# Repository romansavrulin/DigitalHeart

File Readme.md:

# RDC1-0009, Цифровое сердце

Это цифровое, светодиодное сердце будет отличным подарком девушке ко Дню Влюбленных, 8 Марта, или на День рождения.
21 светодиод расположены по периметру печатной платы в виде сердца. Все они управляются микроконтроллером ATmega328. В демонстрационном скетче прописаны несколько эффектов оживляющих сердце. Скетч загружается с помощью любого контроллера Arduino. Но главная изюминка это вибромоторчик от смартфона расположенный на тыльной стороне. Он создает эффект бьющегося в такт световым эффектам сердца. Скетч легко изменить, если вы придумаете новые световые эффекты и частоту стука сердца. 
На тыльной стороне сердца есть зарядное устройство для Li-ion аккумуляторов, которое будет подзаряжать ваше сердце через порт Mini USB. Схема зарядного устройства собрана на микросхеме MCP73831T. Схема включения стандартная из описания на микросхему.
Все детали проекта открыты для свободного использования. Проект созданный в KiCAD можно скачать в приложении. Программу скачивайте в разделе «Скетч – код программы».

## Внешний вид устройства

## Технические параметры

Размер - 50 х 50 мм.
Источник питания – Li-Ion или Li-Pol аккумулятор 3,7В

## Programmer wiring

| Nano pins | NANO ISP PIN | Nano net | Target Net | Target Pin |
|-----|-----|-----|-----|----|
| D12 | 1 | MOSI | MISO | 1 |
| 5V  | 2 | 5V | 5V   | 2 |
| D13 | 3 | SCK | SCK  | 3 |
| D11 | 4 | MISO | MOSI | 4 |
| D10 | N/A, USE D10 | TARGET_RST | RST | 5  |
| GND | 6 | GND | GND  | 6 |

## Troubleshooting

If you get slow effects, it's wrong FUSE configuration. Try to run 

```
"C:\Program Files (x86)\Arduino\hardware\tools\avr/bin/avrdude" "-CC:\Program Files (x86)\Arduino\hardware\tools\avr/etc/avrdude.conf" -v -patmega168p -cstk500v1 -PCOM4 -b19200 -U lfuse:w:0xE2:m
```

from console

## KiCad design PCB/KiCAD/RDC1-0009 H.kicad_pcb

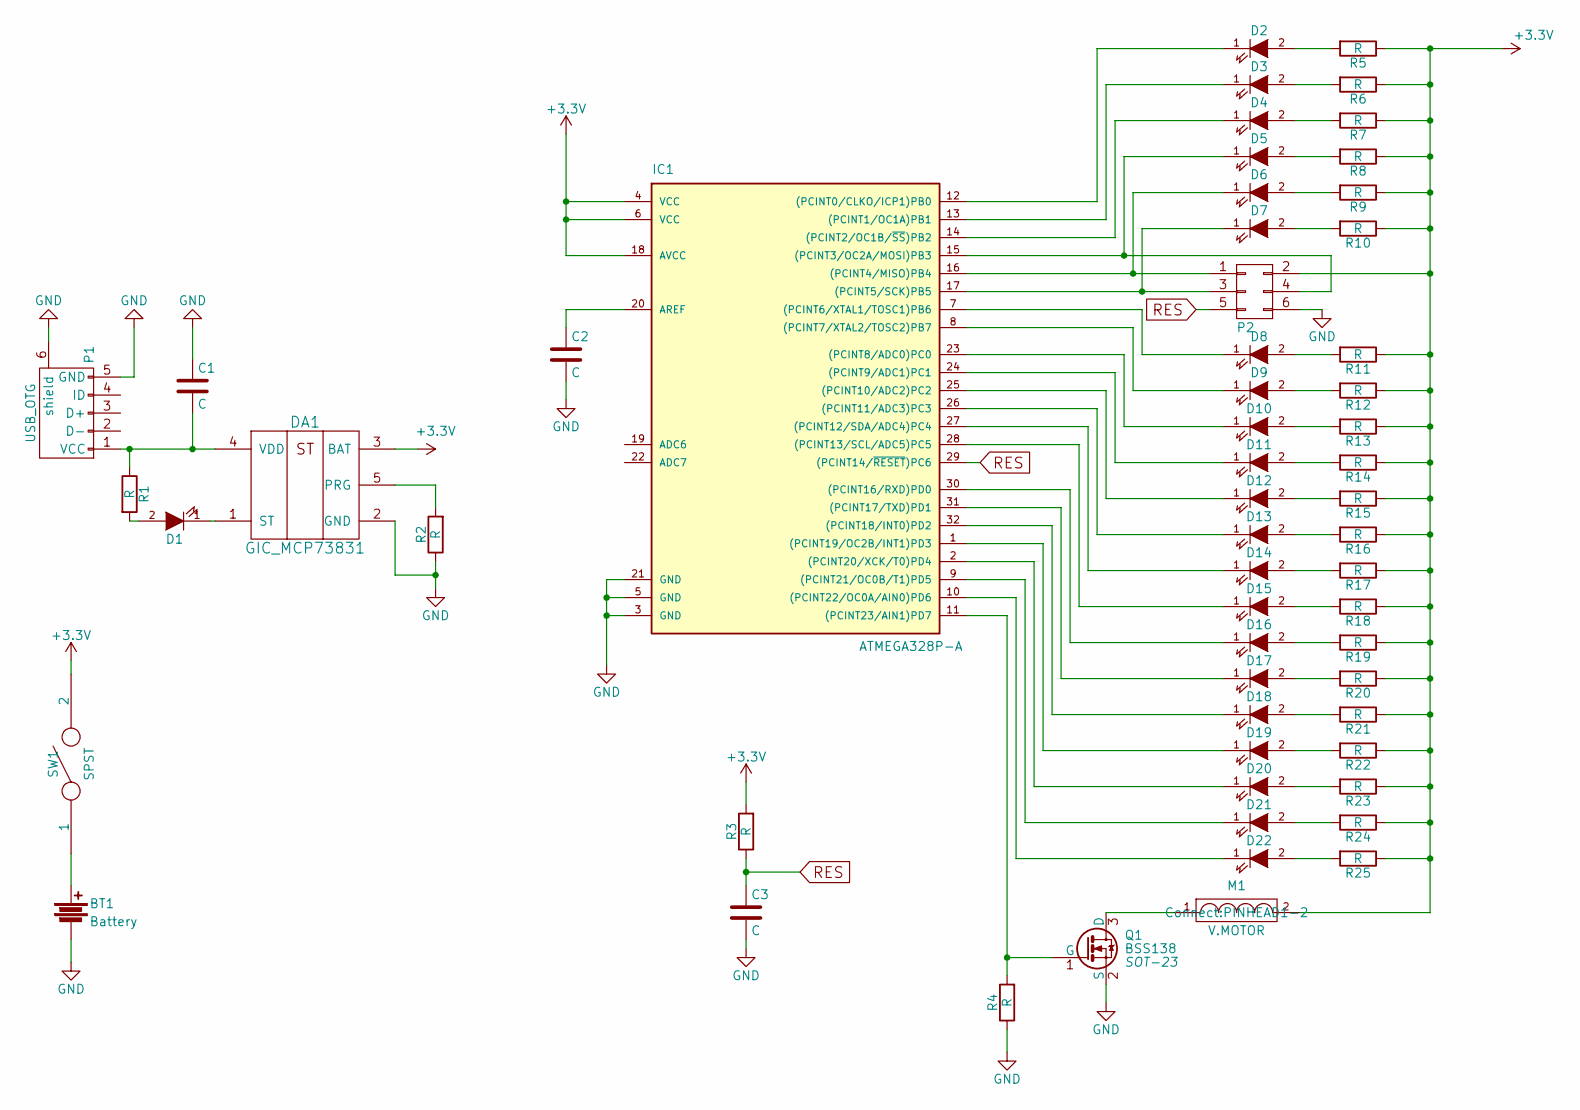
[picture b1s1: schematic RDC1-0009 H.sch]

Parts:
BT1: Battery; Pin_Header_Straight_1x02_mm
C1, C2, C3: C; C_0805_HandSoldering
D1, D2, D3, D4, D5, D6, D7, D8, D9, D10, D11, D12, D13, D14, D15, D16, D17, D18, D19, D20, D21, D22: LED; LED_0805
DA1: GIC_MCP73831; SOT-23-5_mm
IC1: ATMEGA328P-A; LQFP-32_7x7mm_Pitch0.8mm
M1: V.MOTOR; PINHEAD1-2
P1: USB_OTG; USB_Mini-B_mm
P2: CONN_02X03; Pin_Header_Straight_2x03_mm
Q1: BSS138; SOT-23
R1, R2, R3, R4, R5, R6, R7, R8, R9, R10, R11, R12, R13, R14, R15, R16, R17, R18, R19, R20, R21, R22, R23, R24, R25: R; R_0805_HandSoldering
SW1: SPST; SWITCH-mmp122-r

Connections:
+3V3: DA1.3 (BAT), IC1.4 (VCC), IC1.6 (VCC), IC1.18 (AVCC), M1.2, P2.2, R3.2, R5.1, R6.1, R7.1, R8.1, R9.1, R10.1, R11.1, R12.1, R13.1, R14.1, R15.1, R16.1, R17.1, R18.1, R19.1, R20.1, R21.1, R22.1, R23.1, R24.1, R25.1, SW1.2
GND: BT1.2, C1.1, C2.2, C3.2, DA1.2 (GND), IC1.3 (GND), IC1.5 (GND), IC1.21 (GND), P1.5 (GND), P1.6 (shield), P2.6, Q1.2 (S), R2.1, R4.1
unnamed: BT1.1, SW1.1
unnamed: C1.2, DA1.4 (VDD), P1.1 (VCC), R1.1
unnamed: C2.1, IC1.20 (AREF)
unnamed: D1.1 (K), DA1.1 (ST)
unnamed: D1.2 (A), R1.2
unnamed: D2.1 (K), IC1.12 ((PCINT0/CLKO/ICP1)PB0)
unnamed: D2.2 (A), R5.2
unnamed: D3.1 (K), IC1.13 ((PCINT1/OC1A)PB1)
unnamed: D3.2 (A), R6.2
unnamed: D4.1 (K), IC1.14 ((PCINT2/OC1B/~SS~)PB2)
unnamed: D4.2 (A), R7.2
unnamed: D5.1 (K), IC1.15 ((PCINT3/OC2A/MOSI)PB3), P2.4
unnamed: D5.2 (A), R8.2
unnamed: D6.1 (K), IC1.16 ((PCINT4/MISO)PB4), P2.1
unnamed: D6.2 (A), R9.2
unnamed: D7.1 (K), IC1.17 ((PCINT5/SCK)PB5), P2.3
unnamed: D7.2 (A), R10.2
unnamed: D8.1 (K), IC1.7 ((PCINT6/XTAL1/TOSC1)PB6)
unnamed: D8.2 (A), R11.2
unnamed: D9.1 (K), IC1.8 ((PCINT7/XTAL2/TOSC2)PB7)
unnamed: D9.2 (A), R12.2
unnamed: D10.1 (K), IC1.23 ((PCINT8/ADC0)PC0)
unnamed: D10.2 (A), R13.2
unnamed: D11.1 (K), IC1.24 ((PCINT9/ADC1)PC1)
unnamed: D11.2 (A), R14.2
unnamed: D12.1 (K), IC1.25 ((PCINT10/ADC2)PC2)
unnamed: D12.2 (A), R15.2
unnamed: D13.1 (K), IC1.26 ((PCINT11/ADC3)PC3)
unnamed: D13.2 (A), R16.2
unnamed: D14.1 (K), IC1.27 ((PCINT12/SDA/ADC4)PC4)
unnamed: D14.2 (A), R17.2
unnamed: D15.1 (K), IC1.28 ((PCINT13/SCL/ADC5)PC5)
unnamed: D15.2 (A), R18.2
unnamed: D16.1 (K), IC1.30 ((PCINT16/RXD)PD0)
unnamed: D16.2 (A), R19.2
unnamed: D17.1 (K), IC1.31 ((PCINT17/TXD)PD1)
unnamed: D17.2 (A), R20.2
unnamed: D18.1 (K), IC1.32 ((PCINT18/INT0)PD2)
unnamed: D18.2 (A), R21.2
unnamed: D19.1 (K), IC1.1 ((PCINT19/OC2B/INT1)PD3)
unnamed: D19.2 (A), R22.2
unnamed: D20.1 (K), IC1.2 ((PCINT20/XCK/T0)PD4)
unnamed: D20.2 (A), R23.2
unnamed: D21.1 (K), IC1.9 ((PCINT21/OC0B/T1)PD5)
unnamed: D21.2 (A), R24.2
unnamed: D22.1 (K), IC1.10 ((PCINT22/OC0A/AIN0)PD6)
unnamed: D22.2 (A), R25.2
unnamed: DA1.5 (PRG), R2.2
unnamed: IC1.11 ((PCINT23/AIN1)PD7), Q1.1 (G), R4.2
unnamed: M1.1, Q1.3 (D)
RES: C3.1, IC1.29 ((PCINT14/~RESET~)PC6), P2.5, R3.1

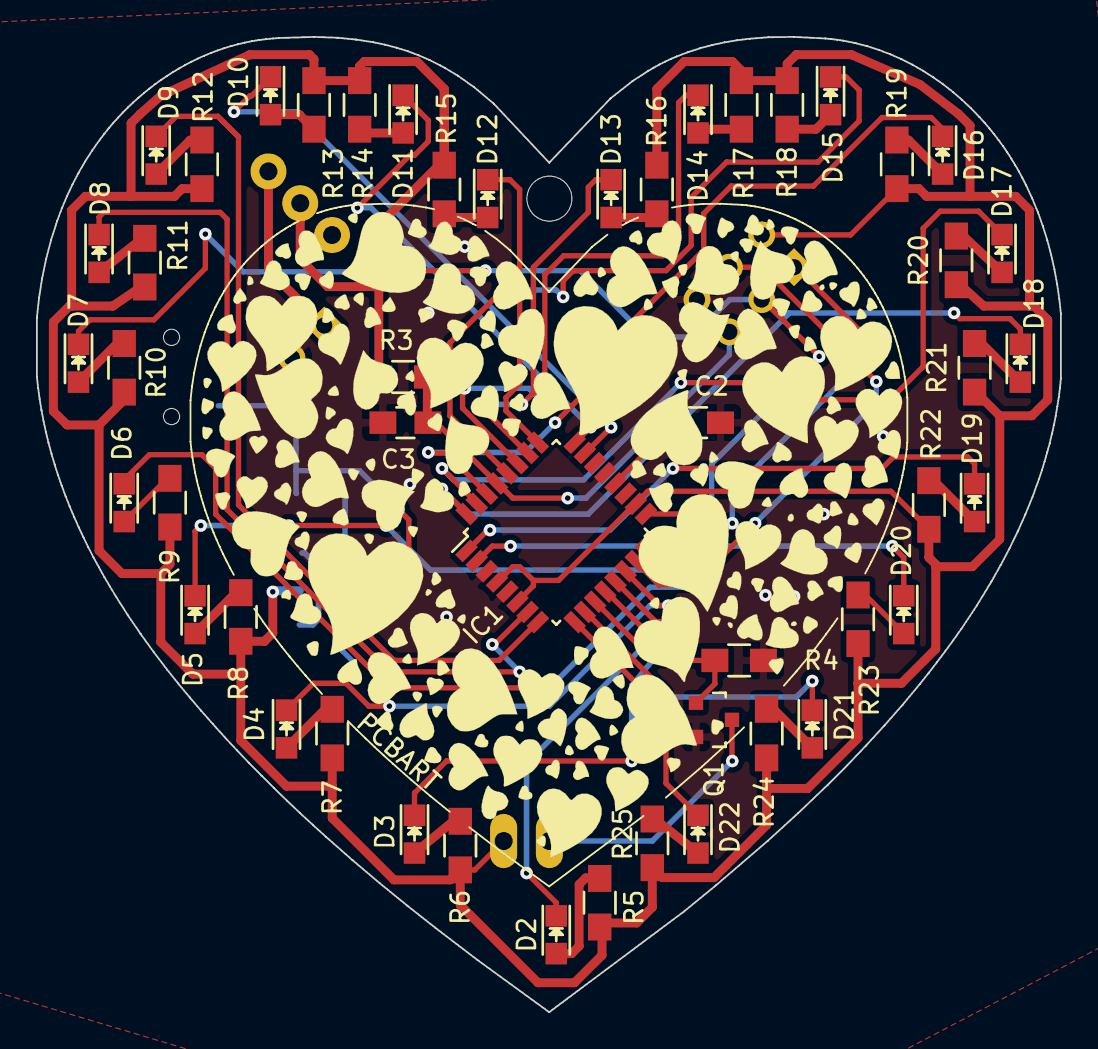
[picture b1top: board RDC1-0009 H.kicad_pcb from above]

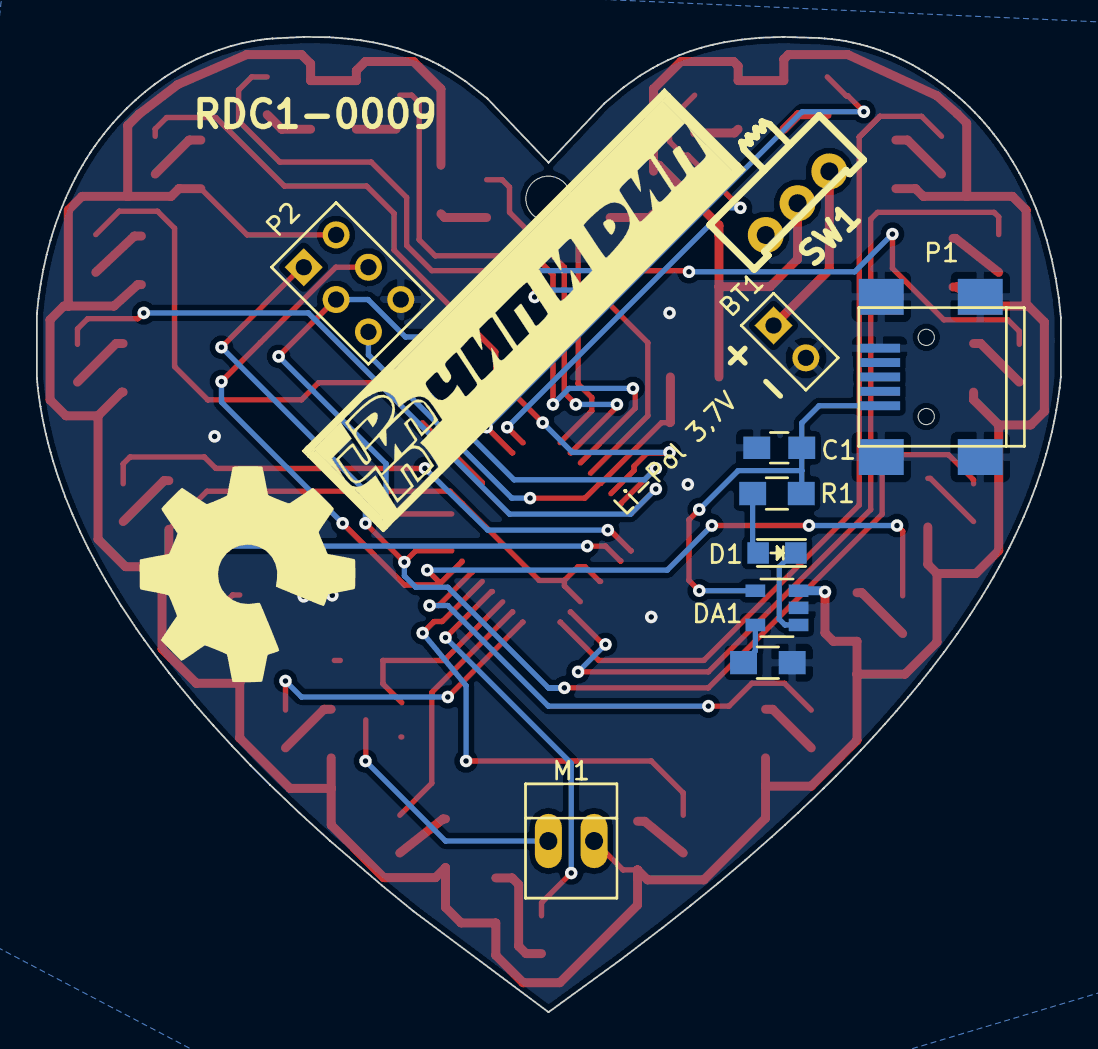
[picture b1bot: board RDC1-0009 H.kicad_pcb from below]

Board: 2 copper layers, 56.9 x 54.2 mm, 58 parts (10 on the bottom side), 53 nets.

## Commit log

2018-04-30 Add PCB related stuff
2018-04-30 Add pictures and Readme from chip-dip
2018-04-30 fix fuses
